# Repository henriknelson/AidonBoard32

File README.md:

# AidonBoard32
KiCad hardware project to facilitate the reading and forwarding of meter value data pushed through the P1-interface on electricity meters produced by Aidon together with a Espressifs ESP32-WROOM module on a single PCB.

3D View:

Schematic:

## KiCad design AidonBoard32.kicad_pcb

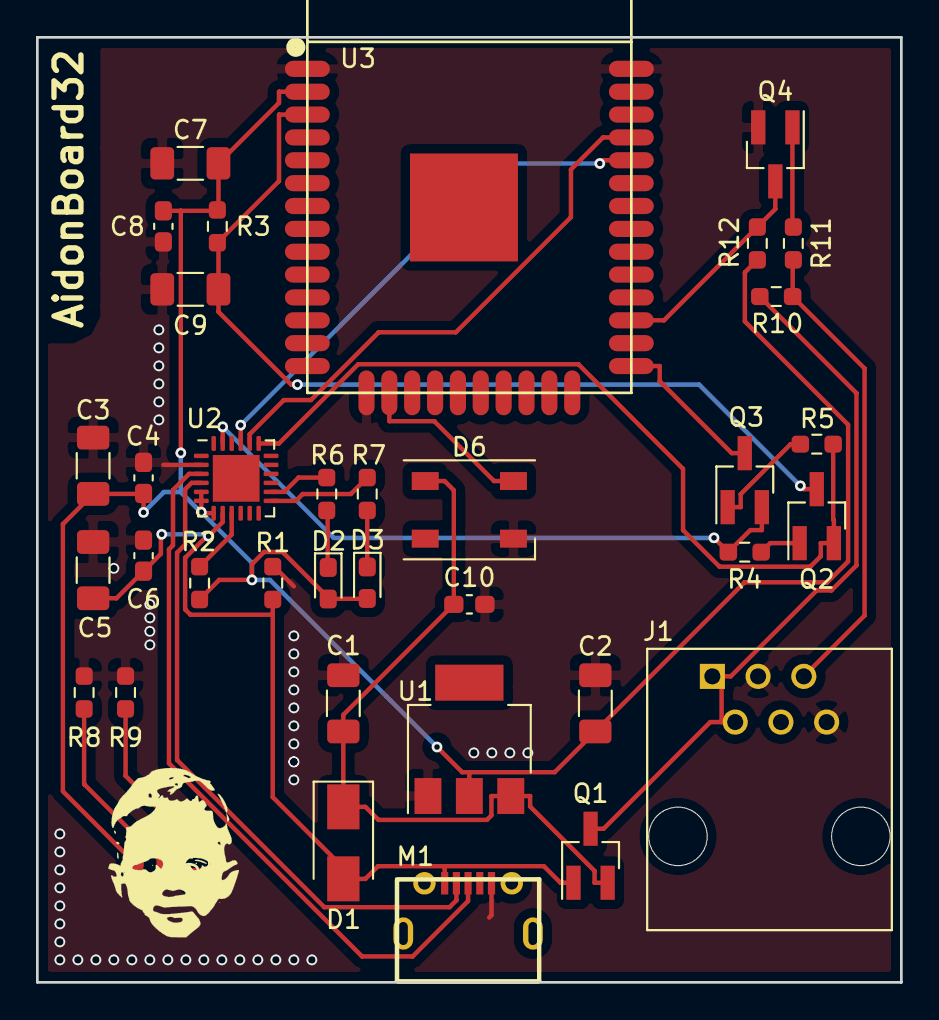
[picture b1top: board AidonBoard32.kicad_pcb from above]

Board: 2 copper layers, 48.0 x 52.5 mm, 38 parts (0 on the bottom side), 26 nets.

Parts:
C1, C2: 22uF; C_1206_3216Metric_Pad1.33x1.80mm_HandSolder
C3, C5: 4.7uF; C_1206_3216Metric_Pad1.33x1.80mm_HandSolder
C4, C6, C8, C10: 0.1uF; C_0603_1608Metric_Pad1.08x0.95mm_HandSolder
C7: 10uF; C_1206_3216Metric_Pad1.33x1.80mm_HandSolder
C9: 1uF; C_1206_3216Metric_Pad1.33x1.80mm_HandSolder
D1: SS54; D_SMA
D2, D3, D4, D5: LED_Small; LED_0603_1608Metric_Pad1.05x0.95mm_HandSolder
D6: WS2812B; LED_WS2812B_PLCC4_5.0x5.0mm_P3.2mm
G1: LOGO; Harry_3
J1: RJ12; TE_5555165-1
M1: U-F-M5DD-Y-L; MICRO_USB_18_TH
Q1: Si2301CDS-T1-GE3; SOT-23_Handsoldering
Q2, Q3, Q4: MMBT3904; SOT-23_Handsoldering
R1: 100K; R_0603_1608Metric_Pad0.98x0.95mm_HandSolder
R2, R11: 1K; R_0603_1608Metric_Pad0.98x0.95mm_HandSolder
R3, R4, R5, R10, R12: 10K; R_0603_1608Metric_Pad0.98x0.95mm_HandSolder
R6, R7, R8, R9: 220; R_0603_1608Metric_Pad0.98x0.95mm_HandSolder
U1: AMS1117-3V3; SOT-223
U2: CP2102N-GQFN24; QFN-24-1EP_4x4mm_P0.5mm_EP2.6x2.6mm
U3: ESP32-WROOM

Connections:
+3V3: C2.1, C3.1, C4.1, C7.1, C8.1, D2.2, D3.2, D4.2, D5.2, R2.2, R3.1, R12.1, U1.2, U2.5, U2.6, U2.7, U3.2
+5V: J1.1, J1.2, Q1.3, R10.1
/D+: M1.3, U2.3
/D-: M1.2, U2.4
/DTR: Q3.2, R4.2, U2.23
/EN: C9.1, Q2.3, R3.2, U3.3
/HAN_OUT: J1.5, R10.2, R11.2
/IO0: Q3.3, U3.25
/IO13: D6.4, U3.16
/LED_RX: R7.1, U2.13
/LED_TX: R6.1, U2.14
/MCU_RX: U2.21, U3.34
/MCU_TX: U2.20, U3.35
/RTS: Q2.2, R5.2, U2.19
/UART_RX: Q4.3, R12.2, U3.27
GND: C1.2, C2.2, C3.2, C4.2, C5.2, C6.2, C7.2, C8.2, C9.2, C10.1, D6.3, J1.3, J1.6, M1.5, Q4.2, R1.2, R8.1, R9.1, U1.1, U2.2, U3.1, U3.15, U3.38
unnamed: D2.1, R6.2
unnamed: D3.1, R7.2
unnamed: D4.1, R8.2
unnamed: D5.1, R9.2
unnamed: Q2.1, R4.1
unnamed: Q3.1, R5.1
unnamed: Q4.1, R11.1
unnamed: R2.1, U2.9
VBUS: C5.1, C6.1, D1.2, M1.1, Q1.1, R1.1, U2.8
VCC: C1.1, C10.2, D1.1, D6.1, Q1.2, U1.3

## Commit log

2021-04-28 Finished first revision of AidonBoard32!
2021-04-29 Fixed routing
2021-04-29 Fixed small issues
2021-04-30 New gerber files
2021-05-11 Updated project with the latest schematic/gerber files/3d renders
2021-05-11 Removed backed up files
2021-05-13 Updated some component values in schematic

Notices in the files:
AidonBoard32.kicad_pcb:
© Henrik Nelson
